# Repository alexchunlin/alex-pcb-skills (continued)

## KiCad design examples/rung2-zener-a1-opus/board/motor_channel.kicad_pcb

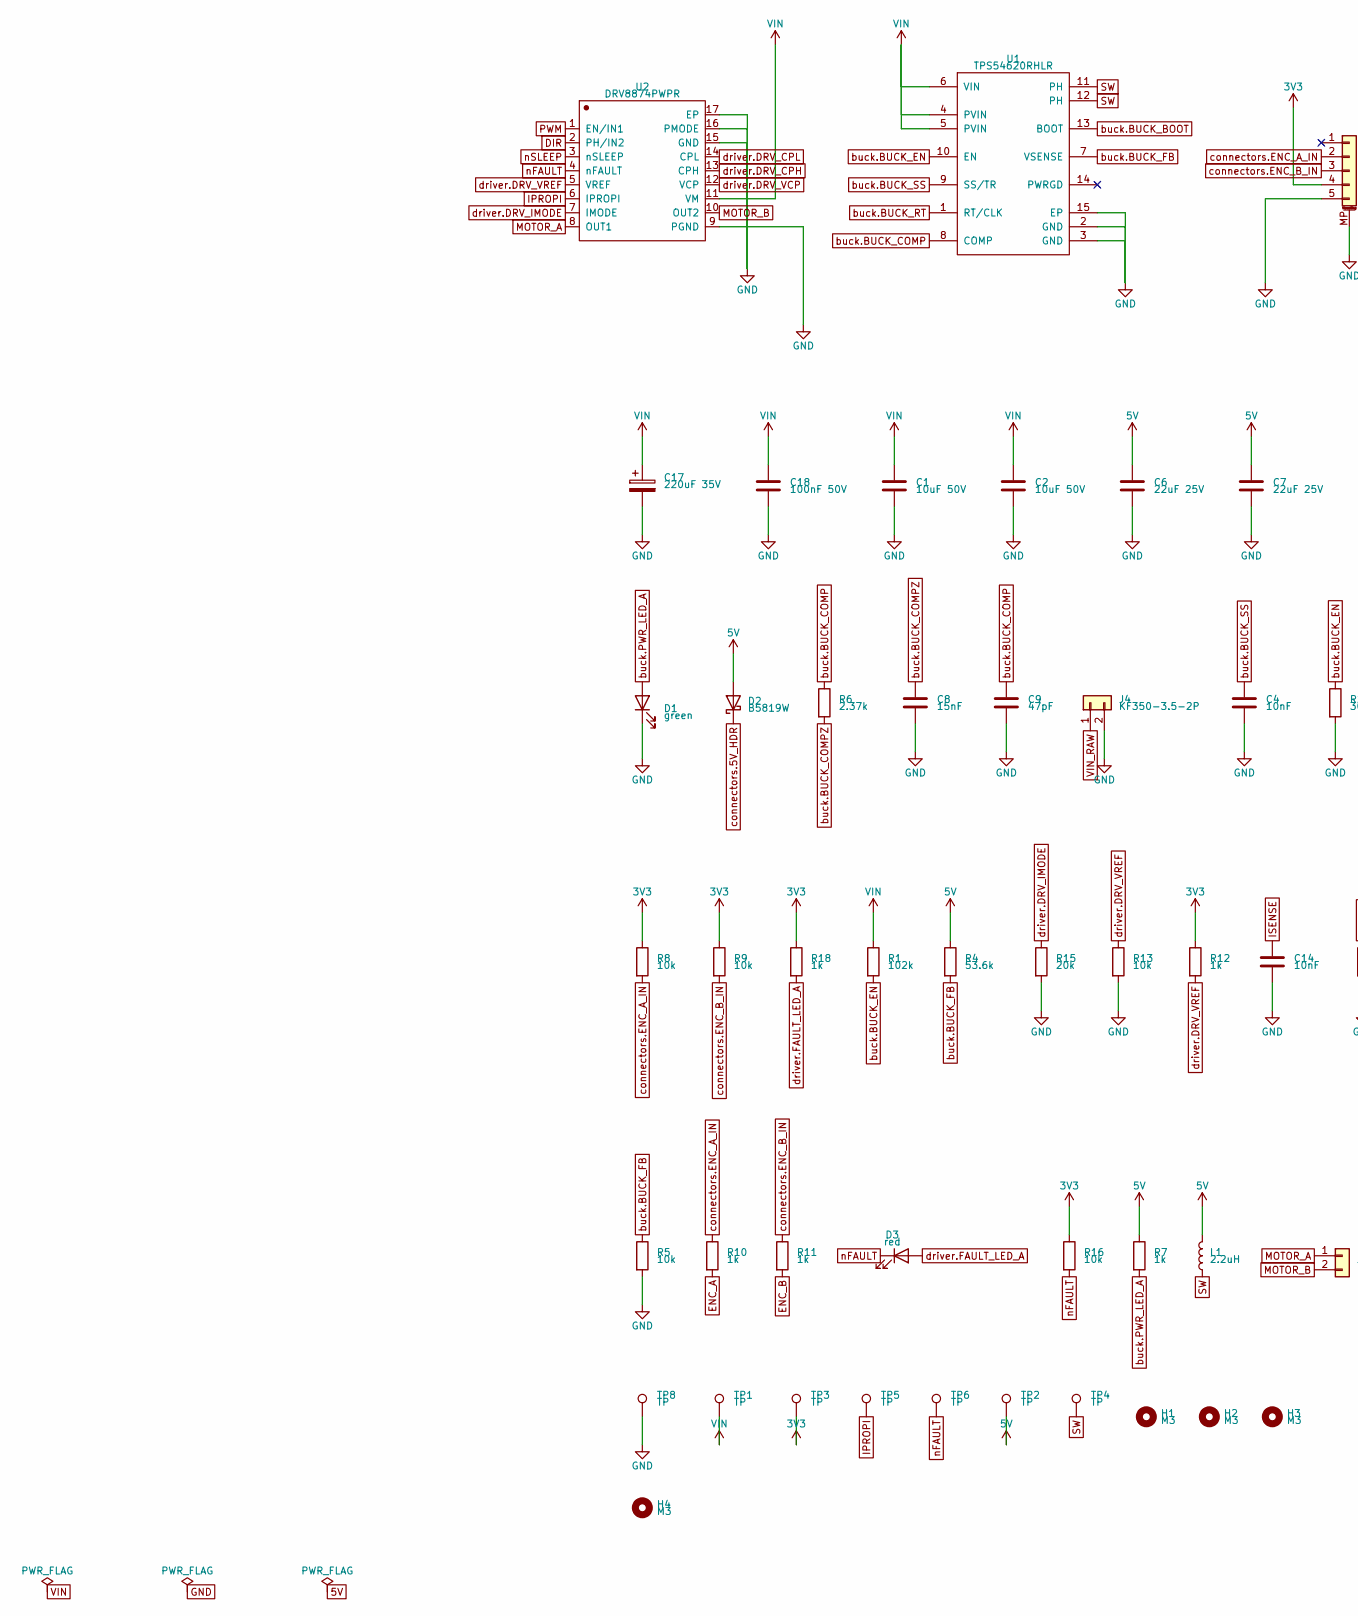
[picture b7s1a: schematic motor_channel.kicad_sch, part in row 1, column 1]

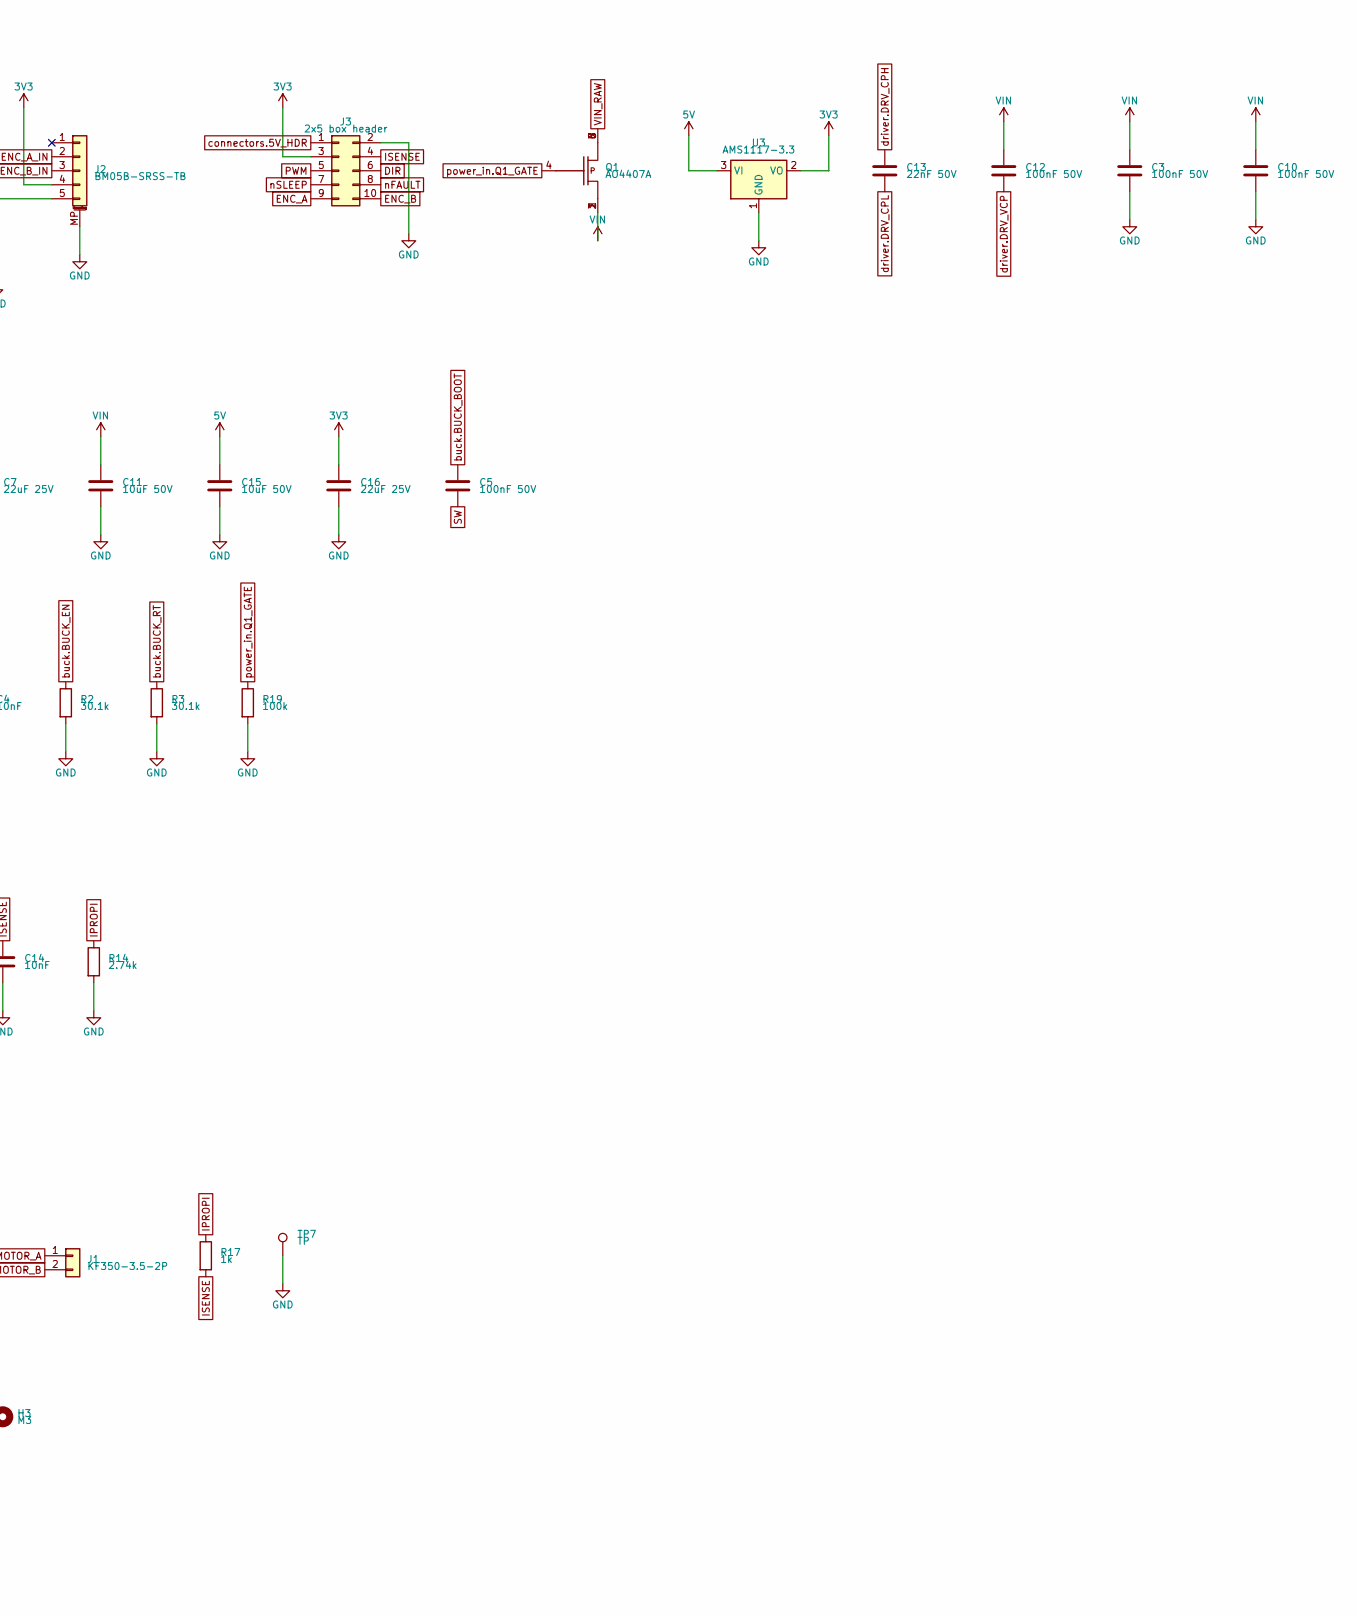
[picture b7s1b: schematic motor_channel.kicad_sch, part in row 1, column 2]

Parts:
C1, C2, C11, C15: 10uF 50V; C_0805_2012Metric; MPN GRM21BR61H106KE43L; LCSC C440198
C3, C5, C10, C12, C18: 100nF 50V; C_0402_1005Metric; MPN CL05B104KB54PNC; LCSC C307331
C4, C14: 10nF; C_0402_1005Metric; MPN CL05B103KB5NNNC; LCSC C15195
C6, C7, C16: 22uF 25V; C_0805_2012Metric; MPN CL21A226MAQNNNE; LCSC C45783
C8: 15nF; C_0402_1005Metric; MPN CC0402KRX7R9BB153; LCSC C114405
C9: 47pF; C_0402_1005Metric; MPN CL05C470JB5NNNC; LCSC C84706
C13: 22nF 50V; C_0402_1005Metric; MPN 0402B223K500NT; LCSC C1532
C17: 220uF 35V; CP_Elec_8x10; MPN BXJ35V220M8*10 8.0TP; LCSC C165523
D1: green; LED_0805_2012Metric; MPN NCD0805G1; LCSC C84260
D2: B5819W; D_SOD-123; MPN B5819W SL; LCSC C8598
D3: red; LED_0805_2012Metric; MPN NCD0805R1; LCSC C84256
H1, H2, H3, H4: M3; MountingHole_3.2mm_M3
J1, J4: KF350-3.5-2P; TerminalBlock_Phoenix_PT-1,5-2-3.5-H_1x02_P3.50mm_Horizontal; MPN KF350-3.5-2P; LCSC C474892
J2: BM05B-SRSS-TB; JST_SH_BM05B-SRSS-TB_1x05-1MP_P1.00mm_Vertical; MPN BM05B-SRSS-TB(LF)(SN); LCSC C160391
J3: 2x5 box header; IDC-Header_2x05_P2.54mm_Vertical; MPN 2.54-2*5P IDC box header; LCSC C3405
L1: 2.2uH; L_Coilcraft_XAL6030-XXX; MPN XAL6030-222MEC; LCSC C5440776
Q1: AO4407A; SOIC-8_3.9x4.9mm_P1.27mm; MPN AO4407A; LCSC C16072
R1: 102k; R_0402_1005Metric; MPN FRC0402F1023TS; LCSC C2933066
R2, R3: 30.1k; R_0402_1005Metric; MPN 0402WGF3012TCE; LCSC C29402
R4: 53.6k; R_0402_1005Metric; MPN 0402WGF5362TCE; LCSC C53398
R5, R8, R9, R13, R16: 10k; R_0402_1005Metric; MPN 0402WGF1002TCE; LCSC C25744
R6: 2.37k; R_0402_1005Metric; MPN 0402WGF2371TCE; LCSC C25881
R7, R10, R11, R12, R17, R18: 1k; R_0402_1005Metric; MPN 0402WGF1001TCE; LCSC C11702
R14: 2.74k; R_0402_1005Metric; MPN 0402WGF2741TCE; LCSC C33360
R15: 20k; R_0402_1005Metric; MPN 0402WGF2002TCE; LCSC C25765
R19: 100k; R_0402_1005Metric; MPN 0402WGF1003TCE; LCSC C25741
TP1, TP2, TP3, TP4, TP5, TP6, TP7, TP8: TP; TestPoint_Pad_D1.5mm
U1: TPS54620RHLR; VQFN-14_L3.5-W3.5-P0.50-TL-EP_TPS54622RHLT; MPN TPS54620RHLR; LCSC C263274
U2: DRV8874PWPR; HTSSOP-16_L5.0-W4.4-P0.65-LS6.4-BL-EP; MPN DRV8874PWPR; LCSC C1855818
U3: AMS1117-3.3; SOT-223-3_TabPin2; MPN AMS1117-3.3; LCSC C6186

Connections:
3V3: C16.1, J2.4, J3.3, R8.1, R9.1, R12.1, R16.1, R18.1, TP3.1, U3.2 (VO)
5V: C6.1, C7.1, C15.1, D2.2 (A), L1.2, R4.1, R7.1, TP2.1, U3.3 (VI)
DIR: J3.6, U2.2 (PH/IN2)
ENC_A: J3.9, R10.2
ENC_B: J3.10, R11.2
GND: C1.2, C2.2, C3.2, C4.2, C6.2, C7.2, C8.2, C9.2, C10.2, C11.2, C14.2, C15.2, C16.2, C17.2, C18.2, D1.1 (K), J2.5, J2.MP (MountPin), J3.2, J4.2, R2.2, R3.2, R5.2, R13.2, R14.2, R15.2, R19.2, TP7.1, TP8.1, U1.2 (GND), U1.3 (GND), U1.15 (EP), U2.9 (PGND), U2.15 (GND), U2.16 (PMODE), U2.17 (EP), U3.1 (GND)
IPROPI: R14.1, R17.1, TP5.1, U2.6 (IPROPI)
ISENSE: C14.1, J3.4, R17.2
MOTOR_A: J1.1, U2.8 (OUT1)
MOTOR_B: J1.2, U2.10 (OUT2)
PWM: J3.5, U2.1 (EN/IN1)
SW: C5.2, L1.1, TP4.1, U1.11 (PH), U1.12 (PH)
VIN: C1.1, C2.1, C3.1, C10.1, C11.1, C12.2, C17.1, C18.1, Q1.1 (S), Q1.2 (S), Q1.3 (S), R1.1, TP1.1, U1.4 (PVIN), U1.5 (PVIN), U1.6 (VIN), U2.11 (VM)
VIN_RAW: J4.1, Q1.5 (D), Q1.6 (D), Q1.7 (D), Q1.8 (D)
buck.BUCK_BOOT: C5.1, U1.13 (BOOT)
buck.BUCK_COMP: C9.1, R6.1, U1.8 (COMP)
buck.BUCK_COMPZ: C8.1, R6.2
buck.BUCK_EN: R1.2, R2.1, U1.10 (EN)
buck.BUCK_FB: R4.2, R5.1, U1.7 (VSENSE)
buck.BUCK_RT: R3.1, U1.1 (RT/CLK)
buck.BUCK_SS: C4.1, U1.9 (SS/TR)
buck.NC_U1_PWRGD: U1.14 (PWRGD)
buck.PWR_LED_A: D1.2 (A), R7.2
connectors.5V_HDR: D2.1 (K), J3.1
connectors.ENC_A_IN: J2.2, R8.2, R10.1
connectors.ENC_B_IN: J2.3, R9.2, R11.1
connectors.NC_J3_Pin_1: J2.1
driver.DRV_CPH: C13.1, U2.13 (CPH)
driver.DRV_CPL: C13.2, U2.14 (CPL)
driver.DRV_IMODE: R15.1, U2.7 (IMODE)
driver.DRV_VCP: C12.1, U2.12 (VCP)
driver.DRV_VREF: R12.2, R13.1, U2.5 (VREF)
driver.FAULT_LED_A: D3.2 (A), R18.2
nFAULT: D3.1 (K), J3.8, R16.2, TP6.1, U2.4 (nFAULT)
nSLEEP: J3.7, U2.3 (nSLEEP)
power_in.Q1_GATE: Q1.4 (G), R19.1

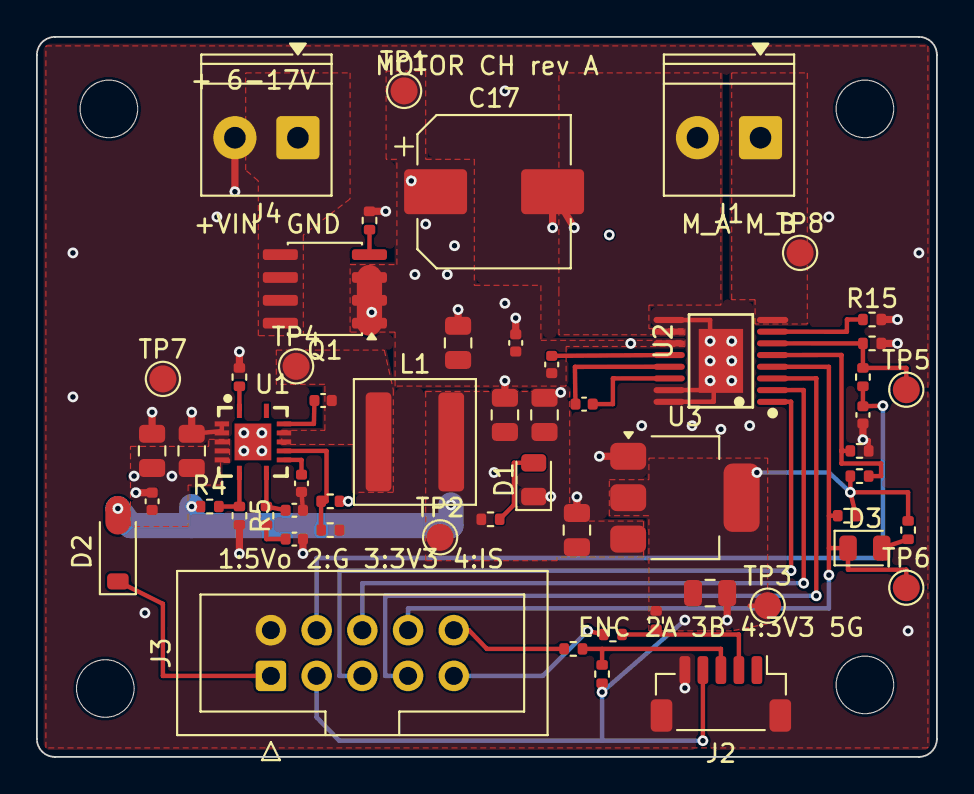
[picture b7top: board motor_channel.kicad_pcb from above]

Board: 4 copper layers, 50.0 x 40.0 mm, 61 parts (1 on the bottom side), 34 nets.

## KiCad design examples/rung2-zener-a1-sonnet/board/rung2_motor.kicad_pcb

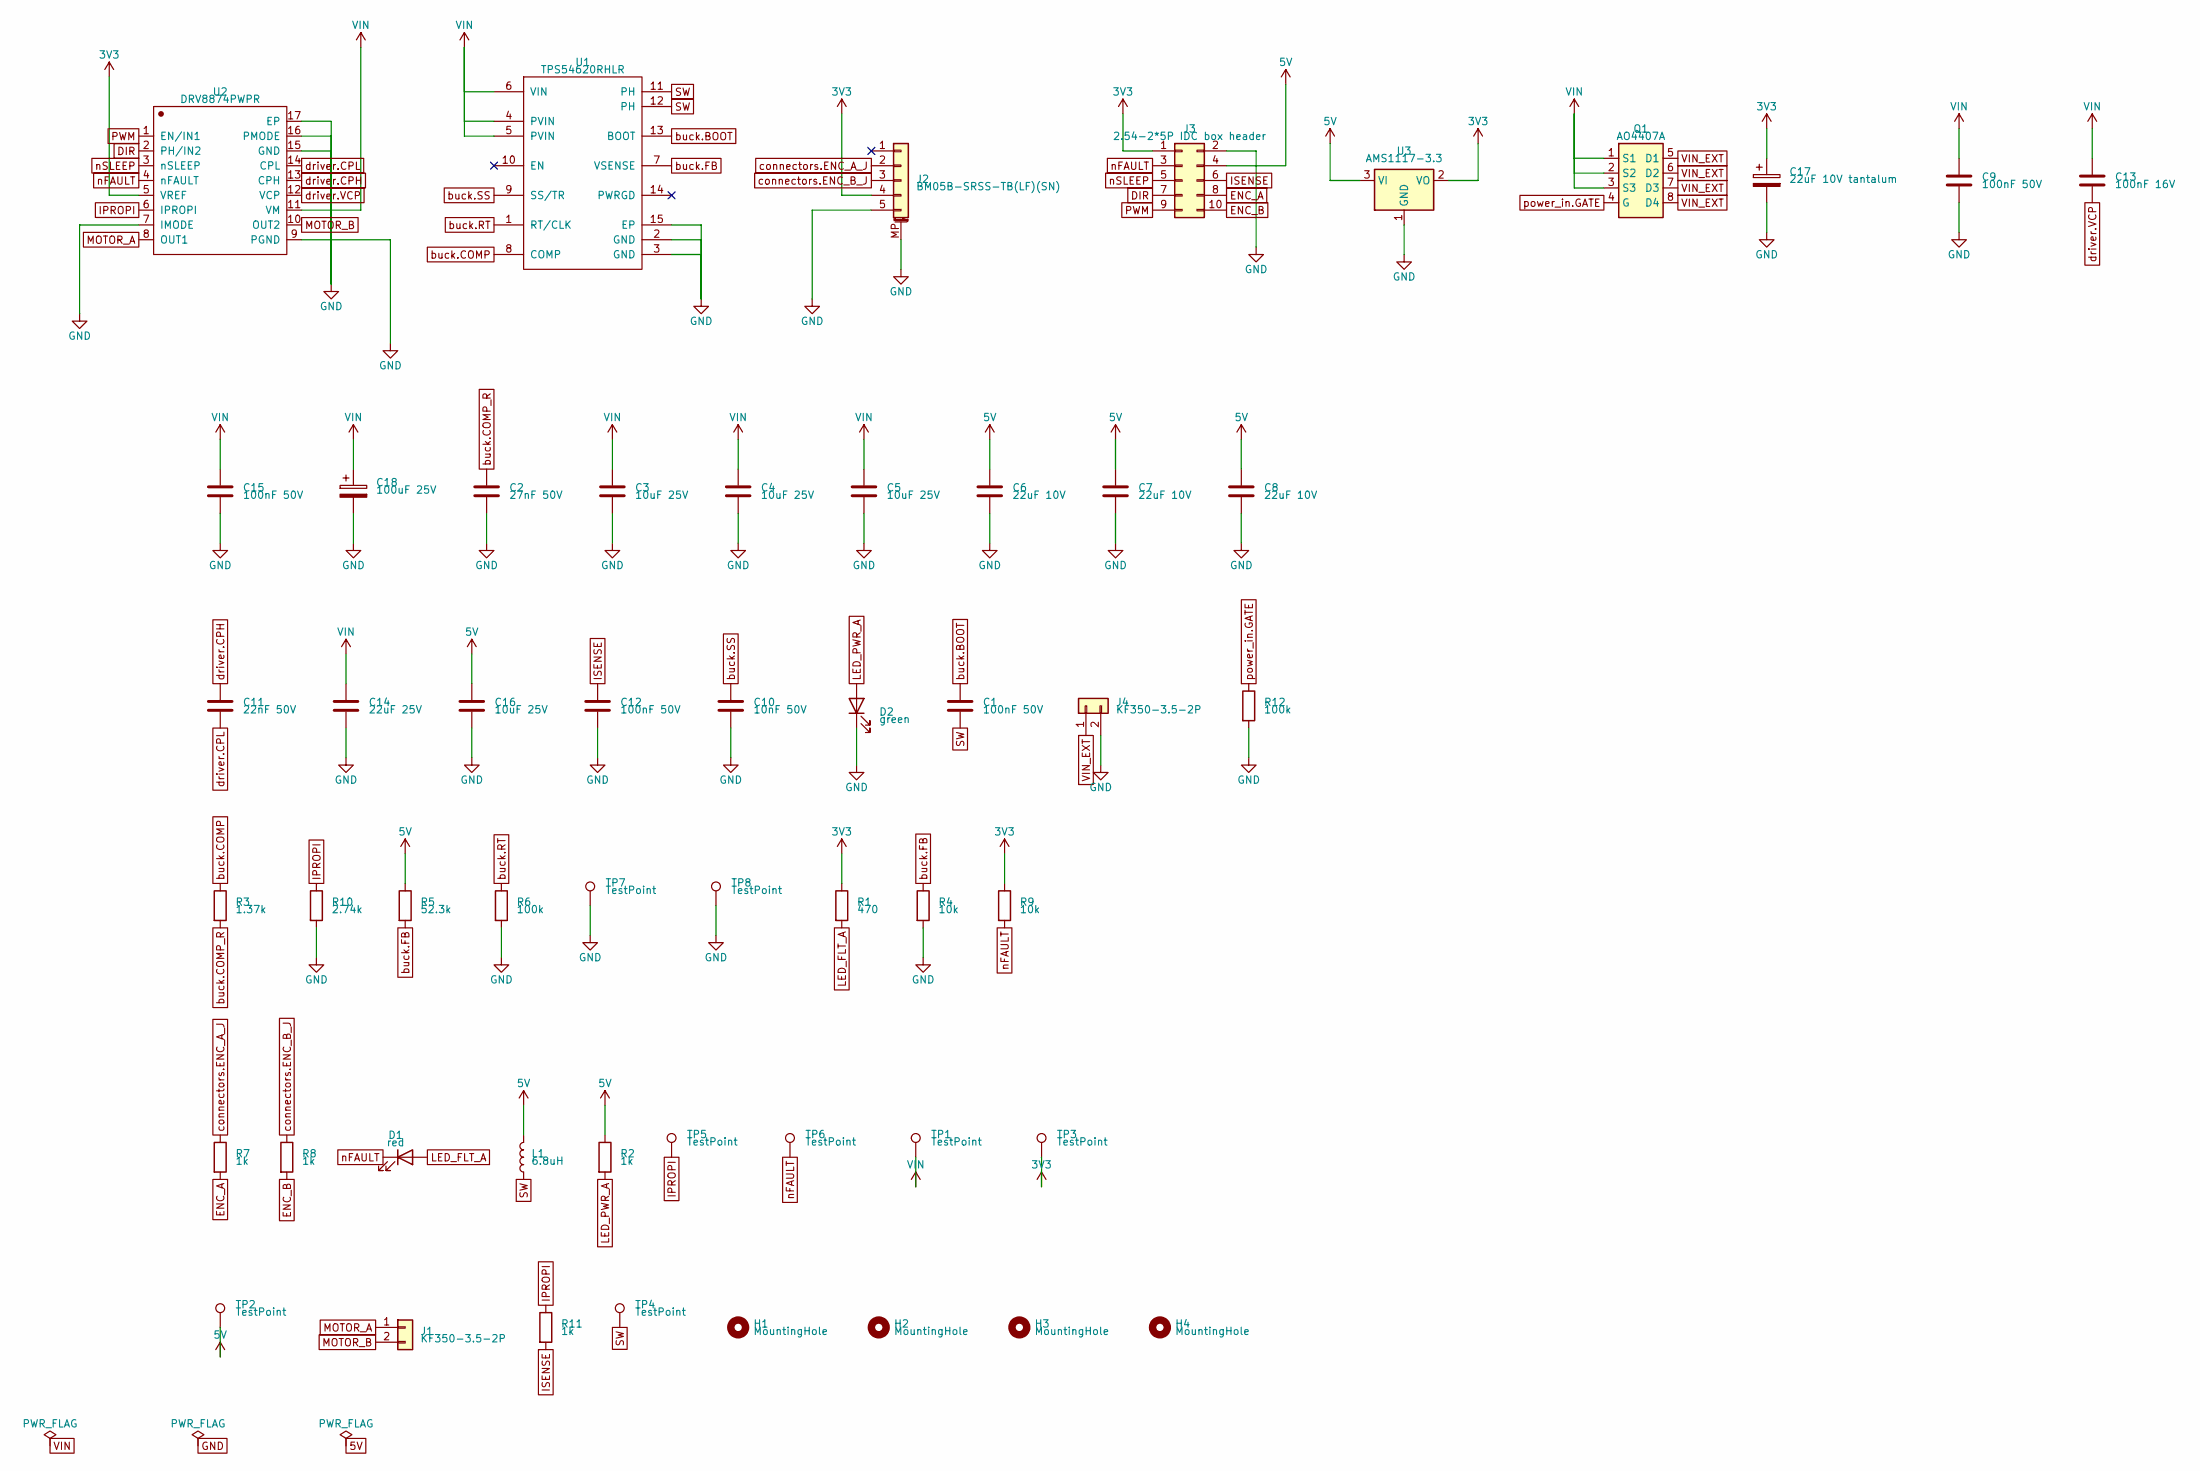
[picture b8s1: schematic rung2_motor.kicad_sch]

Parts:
C1, C9, C12, C15: 100nF 50V; C_0603_1608Metric; MPN CC0603KRX7R9BB104; LCSC C14663
C2: 27nF 50V; C_0603_1608Metric; MPN CC0603KRX7R9BB273; LCSC C107086
C3, C4, C5: 10uF 25V; C_1206_3216Metric; MPN CL31A106KAHNNNE; LCSC C9807
C6, C7, C8: 22uF 10V; C_0805_2012Metric; MPN CL21A226MPQNNNE; LCSC C29277
C10: 10nF 50V; C_0603_1608Metric; MPN CC0603KRX7R9BB103; LCSC C100042
C11: 22nF 50V; C_0603_1608Metric; MPN CC0603KRX7R9BB223; LCSC C106222
C13: 100nF 16V; C_0603_1608Metric; MPN CL10B104KO8NNNC; LCSC C66501
C14: 22uF 25V; C_1210_3225Metric; MPN CL32A226KAJNNNE; LCSC C52306
C16: 10uF 25V; C_0805_2012Metric; MPN CL21A106KAYNNNE; LCSC C15850
C17: 22uF 10V tantalum; CP_EIA-3216-18_Kemet-A; MPN CA45-A-10V-22uF-K; LCSC C129272
C18: 100uF 25V; CP_Elec_6.3x7.7; MPN MVK25V100M6.3*8 6.3TP; LCSC C346943
D1: red; LED_0603_1608Metric; MPN KT-0603R; LCSC C2286
D2: green; LED_0603_1608Metric; MPN KT-0603G; LCSC C12624
H1, H2, H3, H4: MountingHole; MountingHole_3.2mm_M3
J1, J4: KF350-3.5-2P; TerminalBlock_PT-1_5-2-3.5-H; MPN KF350-3.5-2P; LCSC C474892
J2: BM05B-SRSS-TB(LF)(SN); JST_SH_BM05B-SRSS-TB_1x05-1MP_P1.00mm_Vertical; MPN BM05B-SRSS-TB(LF)(SN); LCSC C160391
J3: 2.54-2*5P IDC box header; IDC-Header_2x05_P2.54mm_Vertical; MPN 2.54-2*5P IDC box header; LCSC C5665
L1: 6.8uH; IND-SMD_L7.3-W6.6; MPN FXL0630-6R8-M; LCSC C167221
Q1: AO4407A; SOIC-8_3.9x4.9mm_P1.27mm; MPN AO4407A; LCSC C16072
R1: 470; R_0603_1608Metric; MPN 0603WAF4700T5E; LCSC C23179
R2, R7, R8, R11: 1k; R_0603_1608Metric; MPN 0603WAF1001T5E; LCSC C21190
R3: 1.37k; R_0603_1608Metric; MPN 0603WAF1371T5E; LCSC C22839
R4, R9: 10k; R_0603_1608Metric; MPN 0603WAF1002T5E; LCSC C25804
R5: 52.3k; R_0603_1608Metric; MPN 0603WAF5232T5E; LCSC C23198
R6, R12: 100k; R_0603_1608Metric; MPN 0603WAF1003T5E; LCSC C25803
R10: 2.74k; R_0603_1608Metric; MPN 0603WAF2741T5E; LCSC C22944
TP1, TP2, TP3, TP4, TP5, TP6, TP7, TP8: TestPoint; TestPoint_Pad_D1.5mm
U1: TPS54620RHLR; VQFN-14-EP_TPS54620; MPN TPS54620RHLR; LCSC C263274
U2: DRV8874PWPR; HTSSOP-16-EP_DRV8874; MPN DRV8874PWPR; LCSC C1855818
U3: AMS1117-3.3; SOT-223-3_TabPin2; MPN AMS1117-3.3; LCSC C6186

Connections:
3V3: C17.1, J2.4, J3.1, R1.1, R9.1, TP3.1, U2.5 (VREF), U3.2 (VO)
5V: C6.1, C7.1, C8.1, C16.1, J3.4, L1.2, R2.1, R5.1, TP2.1, U3.3 (VI)
DIR: J3.7, U2.2 (PH/IN2)
ENC_A: J3.8, R7.2
ENC_B: J3.10, R8.2
GND: C2.2, C3.2, C4.2, C5.2, C6.2, C7.2, C8.2, C9.2, C10.2, C12.2, C14.2, C15.2, C16.2, C17.2, C18.2, D2.1 (K), J2.5, J2.MP (MountPin), J3.2, J4.2, R4.2, R6.2, R10.2, R12.2, TP7.1, TP8.1, U1.2 (GND), U1.3 (GND), U1.15 (EP), U2.7 (IMODE), U2.9 (PGND), U2.15 (GND), U2.16 (PMODE), U2.17 (EP), U3.1 (GND)
IPROPI: R10.1, R11.1, TP5.1, U2.6 (IPROPI)
ISENSE: C12.1, J3.6, R11.2
LED_FLT_A: D1.2 (A), R1.2
LED_PWR_A: D2.2 (A), R2.2
MOTOR_A: J1.1, U2.8 (OUT1)
MOTOR_B: J1.2, U2.10 (OUT2)
PWM: J3.9, U2.1 (EN/IN1)
SW: C1.2, L1.1, TP4.1, U1.11 (PH), U1.12 (PH)
VIN: C3.1, C4.1, C5.1, C9.1, C13.2, C14.1, C15.1, C18.1, Q1.1 (S1), Q1.2 (S2), Q1.3 (S3), TP1.1, U1.4 (PVIN), U1.5 (PVIN), U1.6 (VIN), U2.11 (VM)
VIN_EXT: J4.1, Q1.5 (D1), Q1.6 (D2), Q1.7 (D3), Q1.8 (D4)
buck.BOOT: C1.1, U1.13 (BOOT)
buck.COMP: R3.1, U1.8 (COMP)
buck.COMP_R: C2.1, R3.2
buck.FB: R4.1, R5.2, U1.7 (VSENSE)
buck.NC_U2_EN: U1.10 (EN)
buck.NC_U2_PWRGD: U1.14 (PWRGD)
buck.RT: R6.1, U1.1 (RT/CLK)
buck.SS: C10.1, U1.9 (SS/TR)
connectors.ENC_A_J: J2.2, R7.1
connectors.ENC_B_J: J2.3, R8.1
connectors.NC_J3_Pin_1: J2.1
driver.CPH: C11.1, U2.13 (CPH)
driver.CPL: C11.2, U2.14 (CPL)
driver.VCP: C13.1, U2.12 (VCP)
nFAULT: D1.1 (K), J3.3, R9.2, TP6.1, U2.4 (nFAULT)
nSLEEP: J3.5, U2.3 (nSLEEP)
power_in.GATE: Q1.4 (G), R12.1

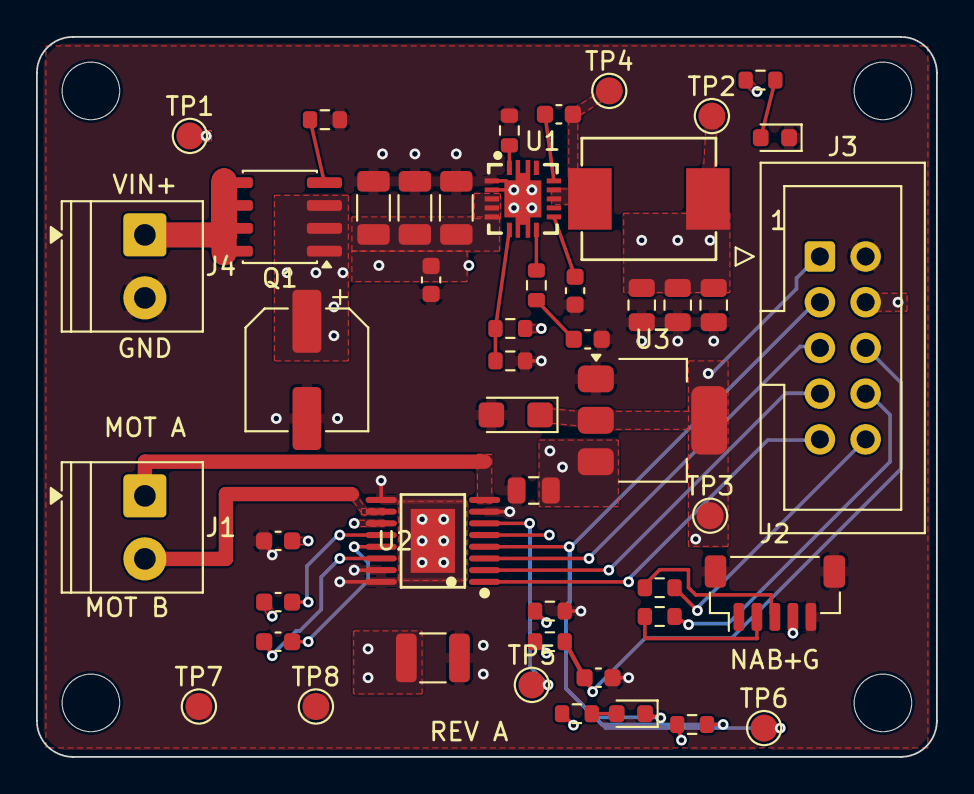
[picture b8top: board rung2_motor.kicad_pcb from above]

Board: 4 copper layers, 50.0 x 40.0 mm, 53 parts (0 on the bottom side), 30 nets.

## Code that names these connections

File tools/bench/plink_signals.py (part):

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
ESP = 3        # ns, assumption: ESP32-S3 GPIO at the default drive strength, 3.3 V CMOS
USB_FS = 4     # ns, USB full-speed edge, spec minimum 4 ns (the ESP32-S3 native USB is full speed, 12 Mb/s)
NFAULT = 20    # ns, assumption: DRV8874 open-drain pull-down, no spec
SW = 3         # ns, assumption as rung 2: the TPS54620 datasheet gives no SW edge rate
GPIO_SRC = f"assumption: ESP32-S3 GPIO, 3.3 V CMOS edge {ESP} ns at the default drive strength"
CH = {"U3": ("m2", "Rp1", "Rmode1", "R10", "R11", "C5", "C3"), "U4": ("m1", "Rp2", "Rmode2", "R12", "R13", "C9", "C7"),
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    sig[n] = {"driver": f"U1 GPIO open-drain (fall), {r} pull-up to +3.3V (rise); I2C", "t_rise_ns": ESP,
              "source": f"the fall is the GPIO's own edge ({GPIO_SRC}); the rise is the pull-up RC", "victim": False,
              "slowed_by": [f"{r} pull-up (rise only)"], "note": "I2C at 400 kHz; four JST drops on the encoder bus"}
for n, pin in (("gpio43", "U0TXD"), ("gpio44", "U0RXD")):
    sig[n] = {"driver": f"U1.{pin} UART, LED through 1k", "t_rise_ns": ESP, "source": GPIO_SRC, "victim": False}
for n in ("gpio21", "gpio35", "gpio36", "gpio37", "gpio38", "gpio39", "gpio40", "gpio41", "gpio42", "gpio47", "gpio48"):
    sig[n] = {"driver": "U1 GPIO to the J4/J7 headers (spare I/O)", "t_rise_ns": ESP, "source": GPIO_SRC + "; use unknown, the edge is the GPIO's",
              "victim": False, "note": "spare header I/O: bucket by the driver's edge, a slower use would relax it"}
sig["Net-(D1-K)"] = {"driver": "gpio44 through LED D1 and R1 1k", "t_rise_ns": ESP, "source": "follows the UART edge through the LED", "victim": False}
sig["Net-(D2-K)"] = {"driver": "gpio43 through LED D2 and R2 1k", "t_rise_ns": ESP, "source": "follows the UART edge through the LED", "victim": False}
sig["Net-(D3-K)"] = {"driver": "+3.3V through LED D3 and R3 1k (power LED)", "t_rise_ns": None, "source": "DC", "victim": False}
sig["boot"] = {"driver": "R8 5.1k pull-up, button J2, header pin; GPIO0 strap", "t_rise_ns": None, "source": "button and RC at boot only", "victim": False}
sig["reset"] = {"driver": "R9 5.1k pull-up, button J3, header pin; EN", "t_rise_ns": None, "source": "button and RC", "victim": False}
for n in ("p26", "p31", "p32", "p33", "p35", "p36", "p37", "p38", "p40"):
    sig[n] = {"driver": "none on this board: J4 to J7 pass-through", "t_rise_ns": None, "source": "no driver on the board", "victim": False}
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             ("Net-(U6-SS/TR)", "U6.9 SS into C18 2.2 nF"), ("Net-(U6-EN)", "+BATT through R16 102k / R17 36.5k (UVLO)")):
    sig[n] = {"driver": d, "t_rise_ns": None, "source": "DC or slow analog", "victim": True}
# IMUs
sig["Net-(U10-C1)"] = {"driver": "U10.4 C1 (LIS3MDL internal cap pin)", "t_rise_ns": None, "source": "DC", "victim": False}
sig["Net-(U10-SD0/SA1)"] = {"driver": "R46 address strap", "t_rise_ns": None, "source": "DC", "victim": False}
sig["Net-(U11-SDO/SA0)"] = {"driver": "R49 address strap", "t_rise_ns": None, "source": "DC", "victim": False}
sig["Net-(U11-CS)"] = {"driver": "R50 pull-up (I2C mode)", "t_rise_ns": None, "source": "DC", "victim": False}
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
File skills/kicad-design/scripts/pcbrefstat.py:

"""Canonical pins, component classes and value bands for the `refstat` rows (spike 2, corpus reference circuits).

Shared by pcbcheck's `refstat` kind and by tools/corpus/refstat.py, which counts the patterns over bshada/open-schematics:
symbol libraries name the same pin differently (AMS1117 VI / VIN / IN, LSM6DS3 "SDO/SA0" / "SA0"), so rows key on a
canonical name. Plain python3, 3.9-compatible (KiCad's bundled Python imports it through pcbcheck).
"""
import re

PART_RX = {
    "AMS1117-3.3": r"AMS1117[-_ ]?(3[.,V]3|33\b)",
    "LSM6DS3": r"LSM6DS3(TR)?(-C)?(?![0-9A-Z])",
    "ESP32-WROOM-32": r"ESP32-WROOM-32",
    "ESP32-S3-WROOM-1": r"ESP32-S3-WROOM-1",
    "DRV8874": r"DRV8874",
    "TPS54620": r"TPS54620",
}
# pin number -> canonical name, used when the symbol's pin name says nothing
BY_NUMBER = {
    "AMS1117-3.3": {"1": "GND", "2": "VOUT", "3": "VIN", "4": "VOUT"},
    "LSM6DS3": {"1": "SA0", "2": "SDX", "3": "SCX", "4": "INT1", "5": "VDDIO", "6": "GND", "7": "GND", "8": "VDD",
                "9": "INT2", "10": "NC", "11": "NC", "12": "CS", "13": "SCL", "14": "SDA"},
    "ESP32-WROOM-32": {"1": "GND", "2": "3V3", "3": "EN", "25": "IO0", "35": "TXD0", "34": "RXD0", "38": "GND", "39": "GND"},
    "ESP32-S3-WROOM-1": {"1": "GND", "2": "3V3", "3": "EN", "27": "IO0", "37": "TXD0", "36": "RXD0", "40": "GND", "41": "GND"},
}


def part_regex(part):
    return re.compile(PART_RX[part], re.I)


def canon_pin(part, num, name):
    n = (name or "").upper().replace(" ", "").replace("~", "").replace("{", "").replace("}", "")
    num = str(num)
    if part == "AMS1117-3.3":
        if "IN" in n:
            return "VIN"
        if "OUT" in n:
            return "VOUT"
        if "GND" in n or "ADJ" in n:
            return "GND"
    elif part == "LSM6DS3":
        for key, c in (("VDDIO", "VDDIO"), ("VDD_IO", "VDDIO"), ("VDD", "VDD"), ("SA0", "SA0"), ("SDX", "SDX"), ("SCX", "SCX"),
                       ("OCS", "OCS"), ("CS", "CS"), ("INT1", "INT1"), ("INT2", "INT2"), ("SCL", "SCL"), ("SPC", "SCL"),
                       ("SDA", "SDA"), ("SDI", "SDA"), ("GND", "GND"), ("NC", "NC")):
            if key in n:
                return c
    elif part in ("ESP32-WROOM-32", "ESP32-S3-WROOM-1"):
        if n in ("3V3", "VDD", "3.3V", "VDD3P3", "VCC", "+3V3"):
            return "3V3"
        if n in ("EN", "CHIP_PU", "CHIP_EN", "RST", "RESET"):
            return "EN"
        if n in ("IO0", "GPIO0", "BOOT", "IO0/BOOT", "GPIO0/BOOT"):
            return "IO0"
        if "GND" in n:
            return "GND"
        if n in ("TXD0", "TX", "U0TXD", "TXD0/IO1", "IO1/TXD0") or (part == "ESP32-WROOM-32" and n in ("IO1", "GPIO1")):
            return "TXD0"
        if n in ("RXD0", "RX", "U0RXD", "RXD0/IO3", "IO3/RXD0") or (part == "ESP32-WROOM-32" and n in ("IO3", "GPIO3")):
            return "RXD0"
    return BY_NUMBER.get(part, {}).get(num) or (n or "#" + num)


def gnd_like(name):
    n = (name or "").upper().lstrip("/")
    return n.startswith(("GND", "VSS", "AGND", "DGND", "PGND", "0V")) or n in ("0", "EARTH", "-")


def power_like(name):
    n = (name or "").upper().lstrip("/")
    return bool(re.match(r"^(\+|VCC|VDD|VBUS|VBAT|VIN|VOUT|VSYS|V\d|\d+V\d*|3V3|5V)", n)) or bool(re.search(r"(^|[_+])\d+V\d*$|3V3|3\.3V|5V0", n))


def comp_class(ref, libpart=""):
    m = re.match(r"^([A-Za-z]+)", ref or "")
    p = (m.group(1) if m else "?").upper()
    lp = (libpart or "").upper()
    if p in ("C", "CP", "CE", "CB"):
        return "C"
    if p in ("R", "RN", "RV"):
        return "R"
    if p in ("FB", "FL") or "FERRITE" in lp or lp.startswith("FB"):
        return "FB"
    if p == "L":
        return "L"
    if p in ("D", "LED", "ZD", "TVS"):
        return "D"
    if p in ("U", "IC"):
        return "U"
    if p in ("J", "P", "CN", "CON", "X"):
        return "J"
    if p in ("SW", "S", "BTN", "K"):
        return "SW"
    if p in ("Q", "T", "M"):
        return "Q"
    if p in ("TP",):
        return "TP"
    if p in ("JP", "SJ"):
        return "JP"
    return p


def parse_value(s):
    """'4.7k' -> 4700, '2k2' -> 2200, '100nF' -> 1e-7, '10u/16V' -> 1e-5, '0.1uF' -> 1e-7; None when not a number."""
    s = (s or "").strip().replace("µ", "u").replace("μ", "u")
    m = re.match(r"^([\d.]+)\s*([pnumkKMGrR]?)\s*(\d*)", s)
    if not m or not m.group(1).replace(".", "", 1).isdigit():
        return None
    whole, unit, frac = m.groups()
    val = float(whole + ("." + frac if frac and "." not in whole else ""))
    return val * {"p": 1e-12, "n": 1e-9, "u": 1e-6, "m": 1e-3, "k": 1e3, "K": 1e3, "M": 1e6, "G": 1e9, "r": 1, "R": 1, "": 1}[unit]


CAP_BANDS = [(1e-9, "pF"), (50e-9, "10n"), (300e-9, "100n"), (3e-6, "1u"), (15e-6, "10u"), (60e-6, "22u"), (1e9, "100u+")]
RES_BANDS = [(100, "R<100"), (1e3, "100R"), (10e3, "1k"), (100e3, "10k"), (1e12, "100k+")]


def value_band(cls, value):
    if cls not in ("C", "R"):
        return "-"
    v = parse_value(value)
    if v is None:
        return "?"
    if cls == "C" and v >= 1e-3:   # a bare "10" or "100" on a capacitor means uF in most hobby schematics
        v = v * 1e-6
    for lim, band in (CAP_BANDS if cls == "C" else RES_BANDS):
        if v < lim:
            return band
    return "?"


PASSIVE = ("C", "R", "L", "FB", "D")


def coarse_band(cls, band):
    """Capacitors split at 1 uF into bypass and bulk; other classes keep their band."""
    if cls != "C" or band in ("?", "-"):
        return band
    return "bypass" if band in ("pF", "10n", "100n") else "bulk"


def band_matches(cls, want, value):
    b = value_band(cls, value)
    return want == "*" or want == b or want == coarse_band(cls, b)
